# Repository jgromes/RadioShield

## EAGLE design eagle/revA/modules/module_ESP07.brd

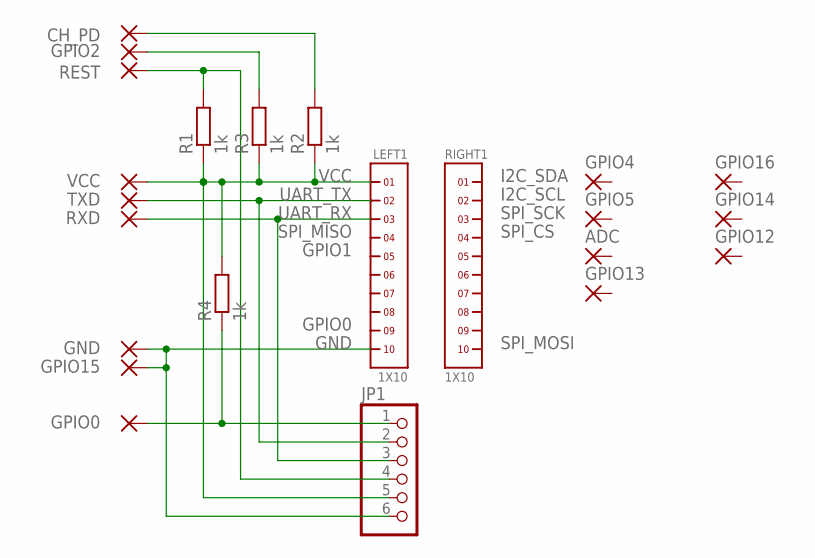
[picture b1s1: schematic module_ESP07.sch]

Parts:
ADC: WIREPADSMD1,27-254; SMD1,27-2,54
CH_PD: WIREPADSMD1,27-254; SMD1,27-2,54
GND: WIREPADSMD1,27-254; SMD1,27-2,54
GPIO0, GPIO2, GPIO4, GPIO5, GPIO12, GPIO13, GPIO14, GPIO15, GPIO16: WIREPADSMD1,27-254; SMD1,27-2,54
JP1: PINHD-1X6; 1X06
LEFT1: 1X10
R1, R2, R3, R4: 1k; R0603
REST: WIREPADSMD1,27-254; SMD1,27-2,54
RIGHT1: 1X10
RXD: WIREPADSMD1,27-254; SMD1,27-2,54
TXD: WIREPADSMD1,27-254; SMD1,27-2,54
VCC: WIREPADSMD1,27-254; SMD1,27-2,54

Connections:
GND: GND.1, GPIO15.1, JP1.6, LEFT1.10
GPIO0: GPIO0.1, JP1.1, R4.1
unnamed: GPIO2.1, R3.2
unnamed: CH_PD.1, R2.2
RST: JP1.4, R1.2, REST.1
UART_RX: JP1.3, LEFT1.3, RXD.1
UART_TX: JP1.2, LEFT1.2, TXD.1
VCC: JP1.5, LEFT1.1, R1.1, R2.1, R3.1, R4.2, VCC.1

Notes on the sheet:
VCC
I2C_SDA
I2C_SCL
SPI_SCK
SPI_CS
SPI_MOSI
UART_TX
UART_RX
SPI_MISO
GPIO1
GPIO0
GND

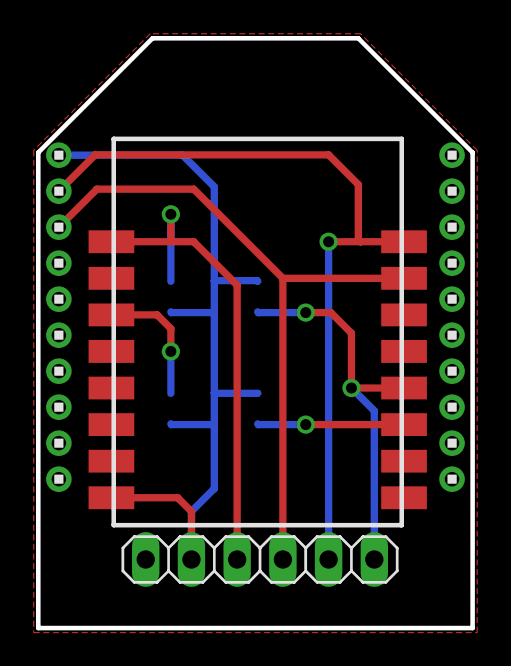
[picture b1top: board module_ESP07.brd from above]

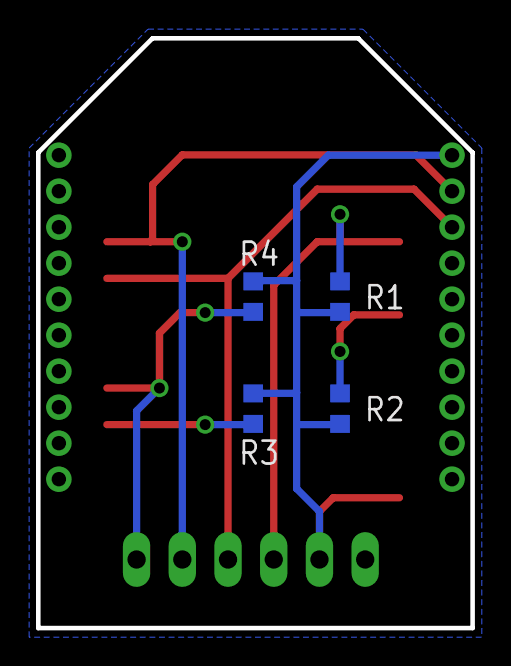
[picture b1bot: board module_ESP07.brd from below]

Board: 2 copper layers, 24.1 x 32.8 mm, 23 parts (4 on the bottom side), 8 nets.

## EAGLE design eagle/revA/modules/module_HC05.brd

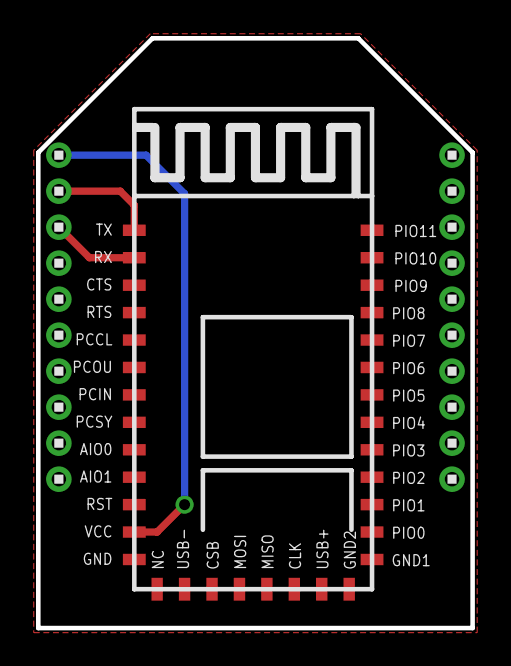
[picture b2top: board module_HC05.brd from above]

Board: 2 copper layers, 24.1 x 32.8 mm, 36 parts (0 on the bottom side), 4 nets.

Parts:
AIO0, AIO1: SMD0,65-1,27
CLK: SMD0,65-1,27
CSB: SMD0,65-1,27
CTS: SMD0,65-1,27
GND, GND1, GND2: SMD0,65-1,27
LEFT1: 1X10
MISO: SMD0,65-1,27
MOSI: SMD0,65-1,27
NC: SMD0,65-1,27
PCCL: SMD0,65-1,27
PCIN: SMD0,65-1,27
PCOU: SMD0,65-1,27
PCSY: SMD0,65-1,27
PIO0, PIO1, PIO2, PIO3, PIO4, PIO5, PIO6, PIO7, PIO8, PIO9, PIO10, PIO11: SMD0,65-1,27
RIGHT1: 1X10
RST: SMD0,65-1,27
RTS: SMD0,65-1,27
RX: SMD0,65-1,27
TX: SMD0,65-1,27
USB+: SMD0,65-1,27
USB-: SMD0,65-1,27
VCC: SMD0,65-1,27

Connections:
GND: GND.1, GND1.1, GND2.1, LEFT1.10
UART_RX: LEFT1.3, RX.1
UART_TX: LEFT1.2, TX.1
VCC: LEFT1.1, VCC.1

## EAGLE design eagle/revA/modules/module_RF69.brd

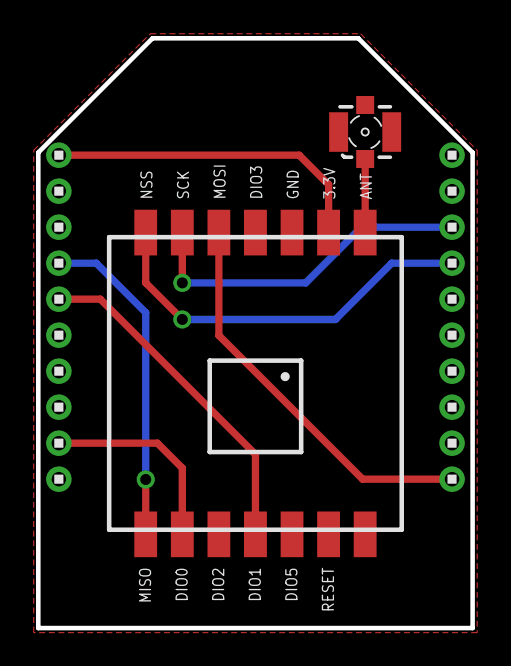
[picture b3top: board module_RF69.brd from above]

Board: 2 copper layers, 24.1 x 32.8 mm, 17 parts (0 on the bottom side), 9 nets.

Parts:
3.3V: SMD1,27-2,54
ANT: SMD1,27-2,54
DIO0, DIO1, DIO2, DIO3, DIO5: SMD1,27-2,54
GND: SMD1,27-2,54
GND_ANT: SMD1,27-2,54
LEFT1: 1X10
MISO: SMD1,27-2,54
MOSI: SMD1,27-2,54
NSS: SMD1,27-2,54
RESET: SMD1,27-2,54
RIGHT1: 1X10
SCK: SMD1,27-2,54
X1: 734120110

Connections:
ANT: ANT.1, X1.1
GND: GND.1, GND_ANT.1, LEFT1.10, X1.S@1, X1.S@2, X1.S@3
INT0: DIO0.1, LEFT1.9
INT1: DIO1.1, LEFT1.5
SPI_CS: NSS.1, RIGHT1.4
SPI_MISO: LEFT1.4, MISO.1
SPI_MOSI: MOSI.1, RIGHT1.10
SPI_SCK: RIGHT1.3, SCK.1
VCC: 3.3V.1, LEFT1.1

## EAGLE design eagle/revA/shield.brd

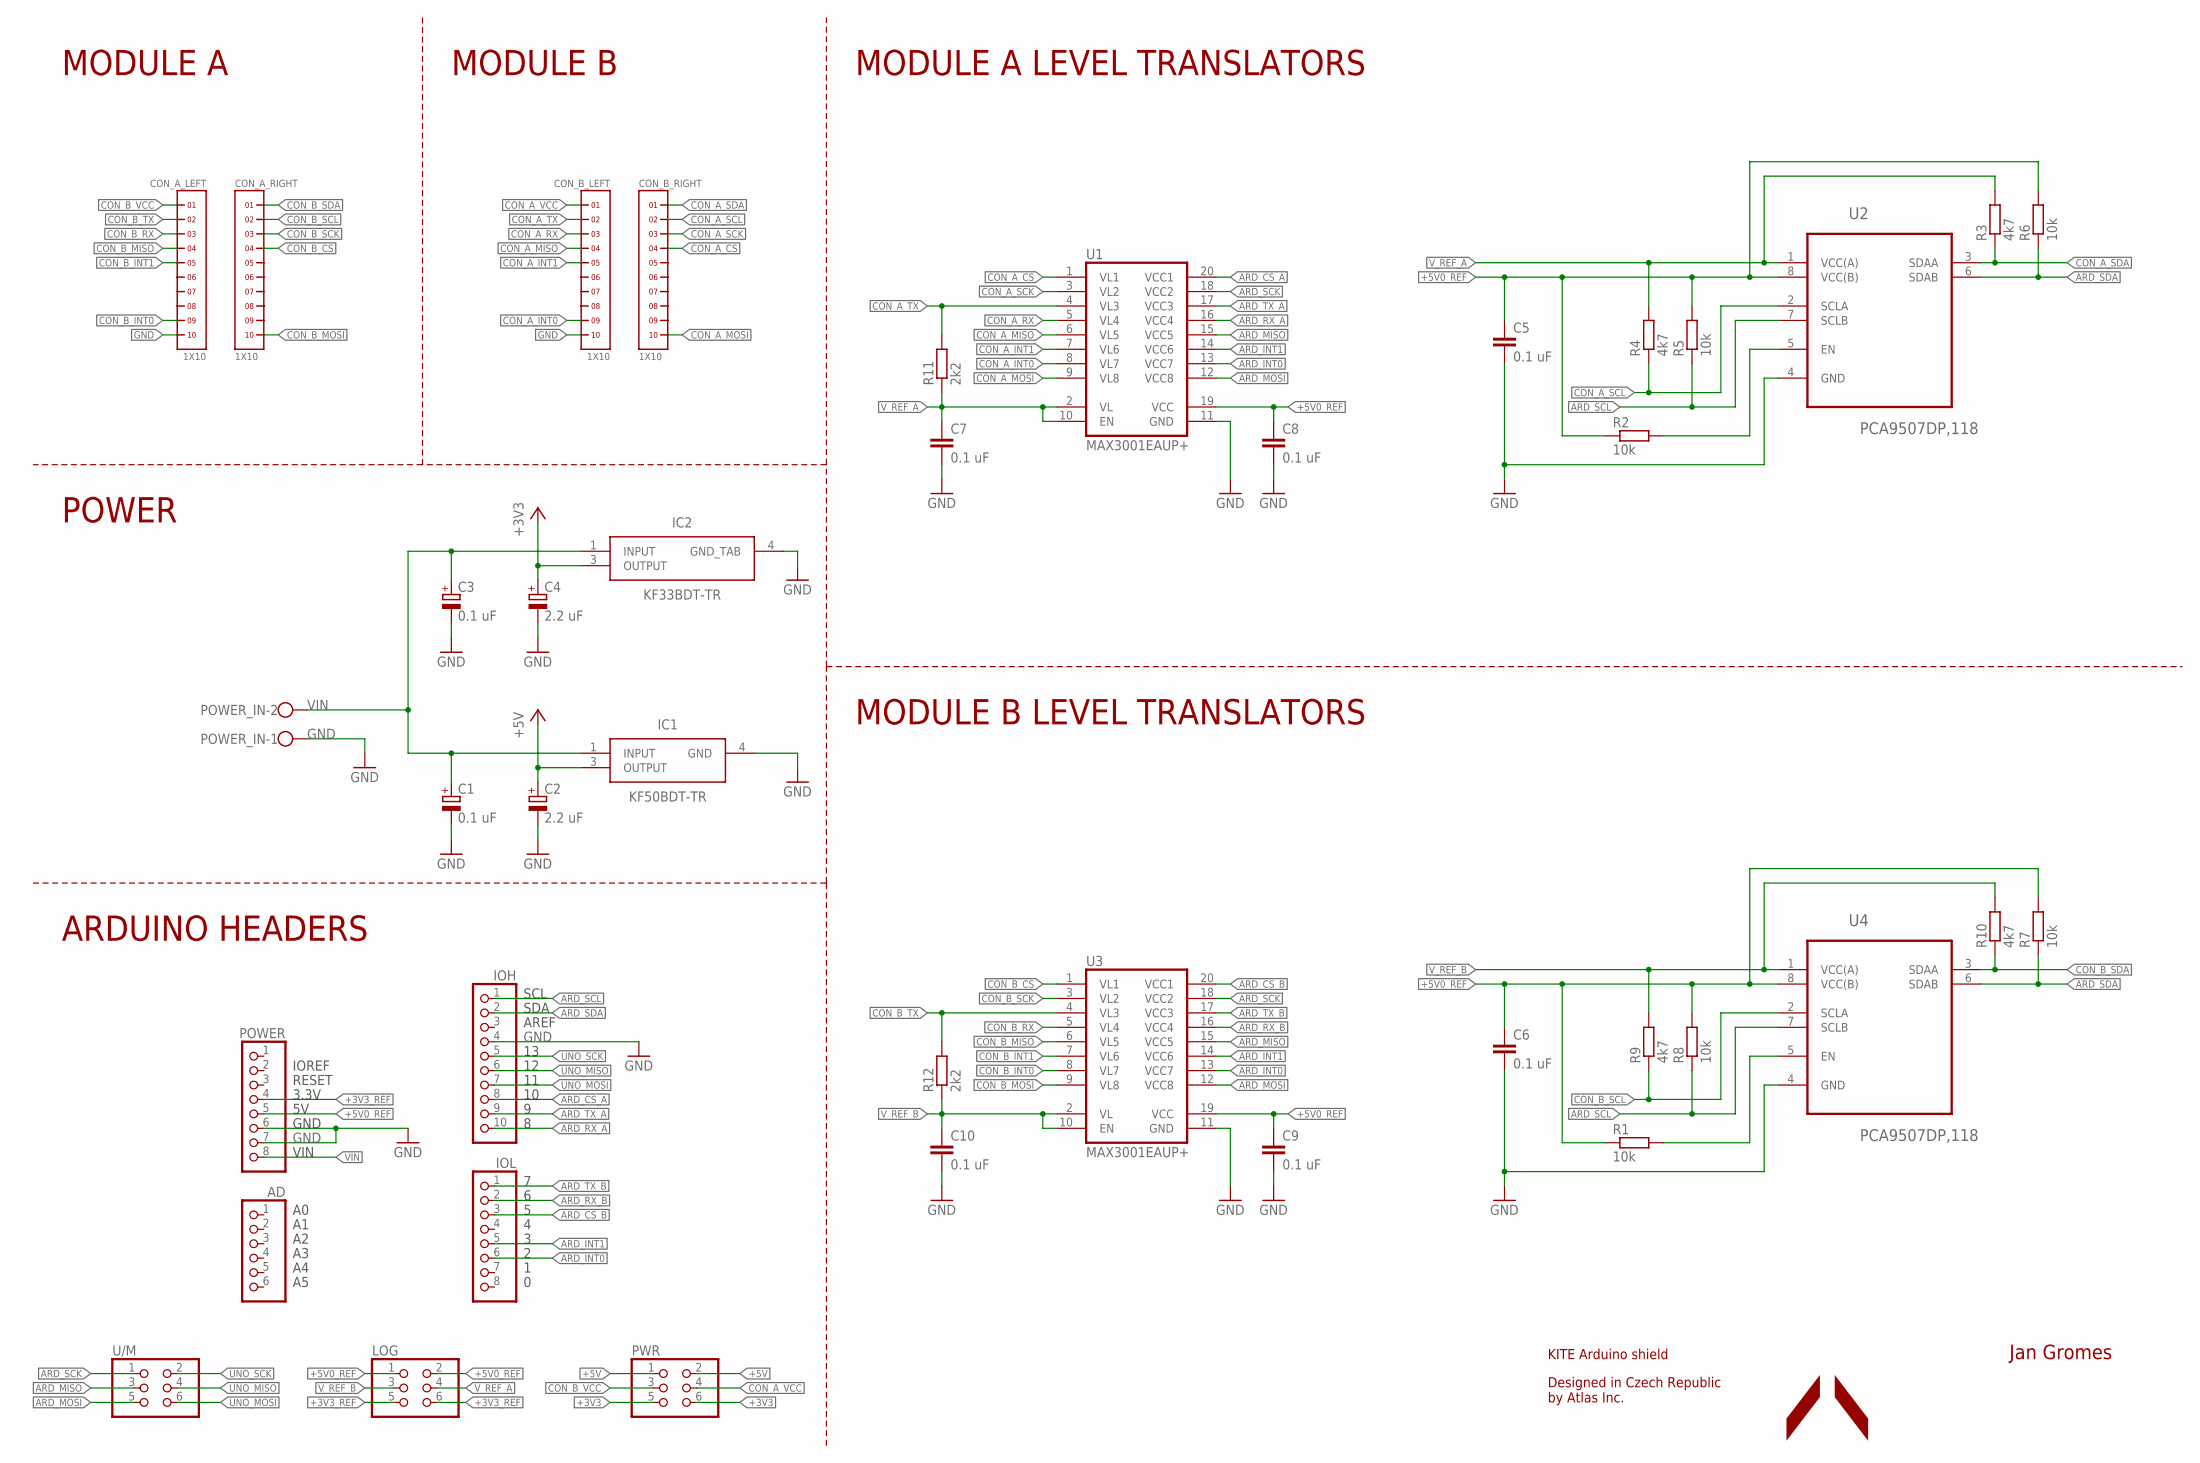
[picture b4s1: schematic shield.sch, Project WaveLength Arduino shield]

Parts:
AD: PINHD-1X6; 1X06
C1, C3: 0.1 uF; SMC_A
C2, C4: 2.2 uF; SMC_A
C5, C6, C7, C8, C9, C10: 0.1 uF; C0603
CON_A_LEFT: 1X10
CON_A_RIGHT: 1X10
CON_B_LEFT: 1X10
CON_B_RIGHT: 1X10
IC1: KF50BDT-TR; TO228P972X240-3N
IC2: KF33BDT-TR; TO228P972X240-3N
IOH: PINHD-1X10; 1X10
IOL: PINHD-1X8; 1X08
LOG: PINHD-2X3; 2X03
POWER: PINHD-1X8; 1X08
POWER_IN: W237-102
PWR: PINHD-2X3; 2X03
R1, R2, R5, R6, R7, R8: 10k; R0603
R3, R4, R9, R10: 4k7; R0603
R11, R12: 2k2; R0603
U1, U3: MAX3001EAUP+; TSSOP20
U2, U4: PCA9507DP,118; SOP65P490X110-8N
U/M: PINHD-2X3; 2X03

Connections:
+3V3: C4.+, IC2.3 (OUTPUT), PWR.5, PWR.6
+3V3_REF: LOG.5, LOG.6, POWER.4
+5V: C2.+, IC1.3 (OUTPUT), PWR.1, PWR.2
+5V0_REF: C5.1, C6.1, C8.1, C9.1, LOG.1, LOG.2, POWER.5, R1.1, R2.1, R5.2, R6.2, R7.2, R8.2, U1.19 (VCC), U2.8 (VCC(B)), U3.19 (VCC), U4.8 (VCC(B))
ARD_CS_A: IOH.8, U1.20 (VCC1)
ARD_CS_B: IOL.3, U3.20 (VCC1)
ARD_INT0: IOL.6, U1.13 (VCC7), U3.13 (VCC7)
ARD_INT1: IOL.5, U1.14 (VCC6), U3.14 (VCC6)
ARD_MISO: U1.15 (VCC5), U3.15 (VCC5), U/M.3
ARD_MOSI: U1.12 (VCC8), U3.12 (VCC8), U/M.5
ARD_RX_A: IOH.10, U1.16 (VCC4)
ARD_RX_B: IOL.2, U3.16 (VCC4)
ARD_SCK: U1.18 (VCC2), U3.18 (VCC2), U/M.1
ARD_SCL: IOH.1, R5.1, R8.1, U2.7 (SCLB), U4.7 (SCLB)
ARD_SDA: IOH.2, R6.1, R7.1, U2.6 (SDAB), U4.6 (SDAB)
ARD_TX_A: IOH.9, U1.17 (VCC3)
ARD_TX_B: IOL.1, U3.17 (VCC3)
CON_A_CS: CON_B_RIGHT.4, U1.1 (VL1)
CON_A_INT0: CON_B_LEFT.9, U1.8 (VL7)
CON_A_INT1: CON_B_LEFT.5, U1.7 (VL6)
CON_A_MISO: CON_B_LEFT.4, U1.6 (VL5)
CON_A_MOSI: CON_B_RIGHT.10, U1.9 (VL8)
CON_A_RX: CON_B_LEFT.3, U1.5 (VL4)
CON_A_SCK: CON_B_RIGHT.3, U1.3 (VL2)
CON_A_SCL: CON_B_RIGHT.2, R4.1, U2.2 (SCLA)
CON_A_SDA: CON_B_RIGHT.1, R3.1, U2.3 (SDAA)
CON_A_TX: CON_B_LEFT.2, R11.2, U1.4 (VL3)
CON_A_VCC: CON_B_LEFT.1, PWR.4
CON_B_CS: CON_A_RIGHT.4, U3.1 (VL1)
CON_B_INT0: CON_A_LEFT.9, U3.8 (VL7)
CON_B_INT1: CON_A_LEFT.5, U3.7 (VL6)
CON_B_MISO: CON_A_LEFT.4, U3.6 (VL5)
CON_B_MOSI: CON_A_RIGHT.10, U3.9 (VL8)
CON_B_RX: CON_A_LEFT.3, U3.5 (VL4)
CON_B_SCK: CON_A_RIGHT.3, U3.3 (VL2)
CON_B_SCL: CON_A_RIGHT.2, R9.1, U4.2 (SCLA)
CON_B_SDA: CON_A_RIGHT.1, R10.1, U4.3 (SDAA)
CON_B_TX: CON_A_LEFT.2, R12.2, U3.4 (VL3)
CON_B_VCC: CON_A_LEFT.1, PWR.3
GND: C1.-, C2.-, C3.-, C4.-, C5.2, C6.2, C7.2, C8.2, C9.2, C10.2, CON_A_LEFT.10, CON_B_LEFT.10, IC1.4 (GND), IC2.4 (GND_TAB), IOH.4, POWER.6, POWER.7, POWER_IN.1, U1.11 (GND), U2.4 (GND), U3.11 (GND), U4.4 (GND)
unnamed: R2.2, U2.5 (EN)
unnamed: R1.2, U4.5 (EN)
UNO_MISO: IOH.6, U/M.4
UNO_MOSI: IOH.7, U/M.6
UNO_SCK: IOH.5, U/M.2
VIN: C1.+, C3.+, IC1.1 (INPUT), IC2.1 (INPUT), POWER.8, POWER_IN.2
V_REF_A: C7.1, LOG.4, R3.2, R4.2, R11.1, U1.2 (VL), U1.10 (EN), U2.1 (VCC(A))
V_REF_B: C10.1, LOG.3, R9.2, R10.2, R12.1, U3.2 (VL), U3.10 (EN), U4.1 (VCC(A))

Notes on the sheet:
Jan Gromes
AREF
SDA
SCL
VIN
GND
3.3V
RESET
IOREF
MODULE B LEVEL TRANSLATORS
MODULE A LEVEL TRANSLATORS
MODULE A
MODULE B
POWER
ARDUINO HEADERS
KITE Arduino shield
Designed in Czech Republic by Atlas Inc.

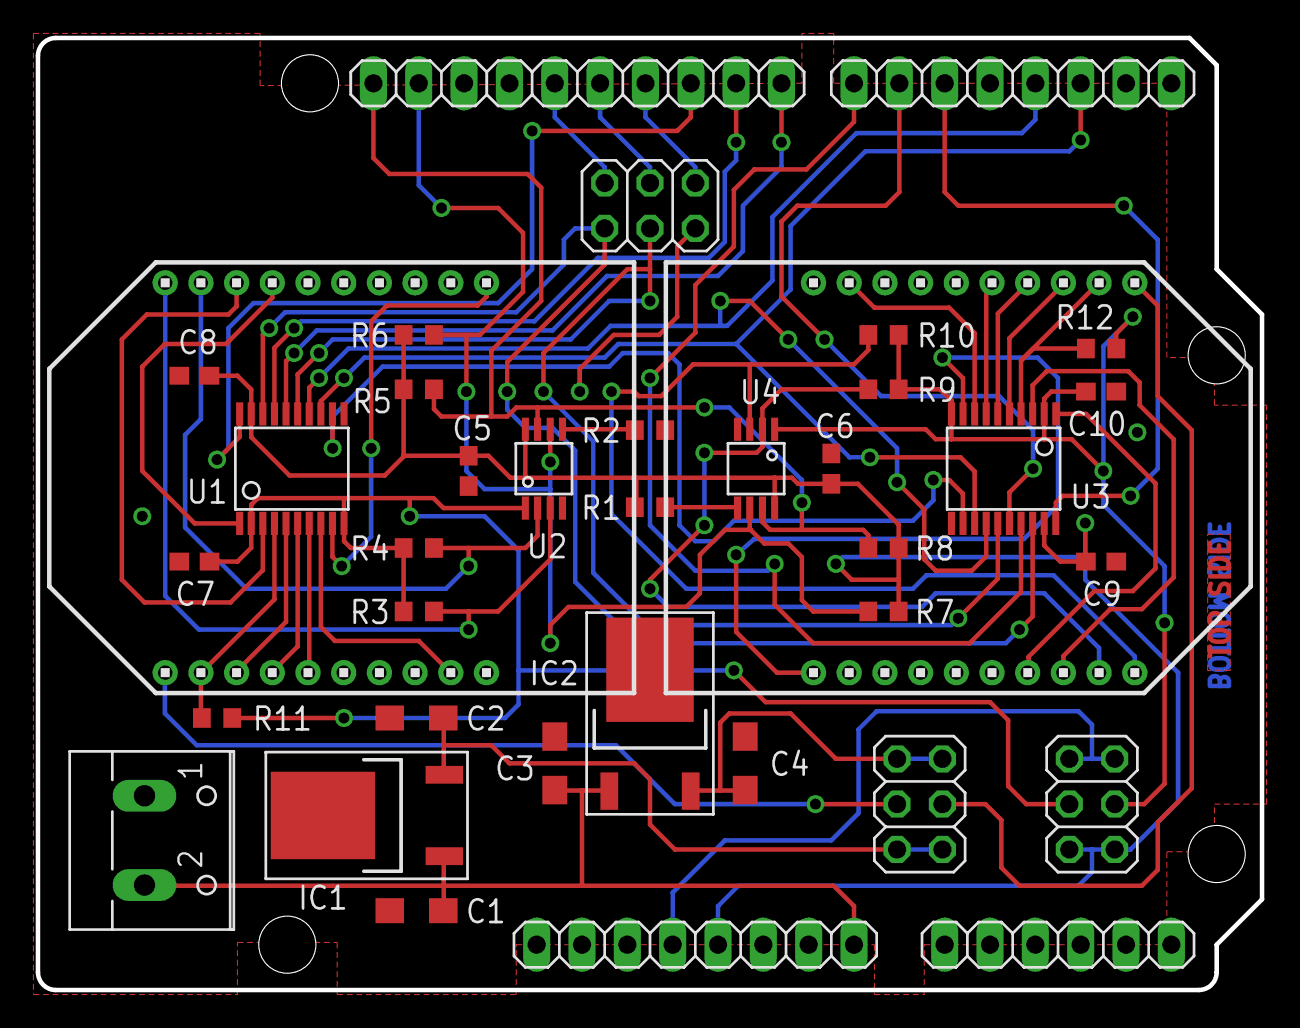
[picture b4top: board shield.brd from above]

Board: 2 copper layers, 68.6 x 53.3 mm, 40 parts (0 on the bottom side), 48 nets.
